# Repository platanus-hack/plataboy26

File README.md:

# Plataboy 26

A pocket game console built around an 8-pin, 10-cent RISC-V microcontroller (CH32V003:
16 KiB flash, 2 KiB RAM), a 128×64 OLED and a coin cell. It was made as merch for
Platanus Hack 26.

| | |
|---|---|
| CPU | WCH CH32V003J4M6: 32-bit RISC-V (QingKe V2A core, RV32EC, no hardware multiplier), 8-pin SOP, up to 48 MHz |
| Flash | 16 KiB, holds the game being played |
| RAM | 2 KiB |
| Storage | 128 KiB I2C EEPROM (AT24CM01): the compressed game library, game data and saves |
| Display | 0.96" monochrome OLED, 128×64, SSD1306 over I2C at 400 kHz |
| Input | four directions, A and B |
| Sound | magnetic buzzer on one pin |
| Power | CR2032 coin cell or, better, a rechargeable LIR2032 (see the note below); slide switch |
| Size | 35.56 × 54.8 mm, two layers |

> [!IMPORTANT]
> **About the battery.** The console draws far more current than a coin cell is made for:
> 17 mA in the menu and up to 33 mA in a game with a bright screen, measured on a board at 3.3 V
> (about 20 mA in a typical game). Coin cells are rated at a fraction of a milliamp.
>
> - **The CR2032 that comes with the board does not last long.** Expect a few hours of play,
>   about 6 at best, and less with bright games or sound. Under this load its voltage sags, so
>   the screen dims and the low-battery beep (below 2.8 V) comes well before the cell is empty.
>   It cannot be recharged: never put a CR2032 in a charger.
> - **A rechargeable LIR2032 is the better choice.** It holds less (35–70 mAh depending on the
>   brand, against roughly 120 mAh usable from a CR2032 at this current), so a charge gives
>   about 2 to 3 hours, but it delivers the current without sagging and can be recharged
>   hundreds of times in an external LIR2032 charger. It fits the same holder with no changes:
>   the board, like the original console, is designed for either cell.
>   A source of good cells: [this AliExpress listing](https://www.aliexpress.com/item/1005008569843235.html).
>
> To stretch either one, lower the contrast in the menu's Settings card (the lowest level takes
> the typical draw from about 20 mA to 12 mA) and switch the console off when not playing. These
> play times are estimates from the measured current and typical cell capacities, not from
> timed runs.

This repository holds everything needed to build one and to write games for it:

| | |
|---|---|
| [`hardware/`](hardware/) | board rev. 1.3.1: circuit, PCB, manufacturing package, checks, 3D model |
| [`games/`](games/) | the ported games, the starter template and the board test programs |
| [`firmware/`](firmware/) | the game library: menu, loader kernel and the packer that fills the EEPROM |
| [`sim/`](sim/) | a simulator that runs the unmodified firmware binaries (CLI and browser) |
| [`art/`](art/) | boot animation and the menu cards of the games |
| [`tools/`](tools/) | `setup.sh`, which downloads the RISC-V GCC toolchain |

## Based on wagiminator's CH32V003 Mini Game Console

The console is a derivative of the
**[CH32V003 Mini Game Console](https://github.com/wagiminator/CH32V003-GameConsole)** by
Stefan Wagner (wagiminator), published under
[CC BY-SA 3.0](https://creativecommons.org/licenses/by-sa/3.0/). The original board (rev. 1.1
here), its driver files and its "Tiny" games (ports of the
[TinyJoypad](https://www.tinyjoypad.com/) games by Daniel Champagne) are his work. The board in
this repository is shared under the same license.

### What changed from the original

**Hardware** (details and the checks behind each point in [`hardware/README.md`](hardware/README.md)):

- **External memory.** A 128 KiB I2C EEPROM (AT24CM01) with its decoupling capacitor, on the
  OLED's bus. The original holds one game at a time in the MCU's 16 KiB of flash; the EEPROM
  holds a compressed library of games, their data and their saves. No MCU pin changes.
- **I2C pull-ups** on the board (2 × 10 kΩ). The original relied on those of the OLED module.
- **A second action button, B.** All eight MCU pins were taken, so B shares the pin of A through
  a resistor divider and is read with the ADC. Games written for the original see only A and run
  unchanged.
- **Parts moved.** A and the buzzer moved to make room for B (A up-right, B down-left, buzzer in
  the bottom-right corner). Every other part keeps its original position, and every original net
  is reproduced (checked against the original Gerbers).
- **Board 4 mm taller** (35.56 × 54.8 mm), with three M2 mounting holes: top corners and bottom
  centre.
- **LCSC footprints** for every assembled part, so that the assembly house places them as drawn.
  That check found the coin cell holder reversed in the first layout.
- **New artwork**: black solder mask, white silkscreen, event logos on the front, a banana
  version of the Pioneer plaque on the back.
- **Generated, not drawn.** The circuit is a Python (SKiDL) file and the PCB is placed, routed
  and checked by scripts (`hardware/make.sh`).

**Software:**

- **Game library firmware.** A menu with a boot animation and a picture card per game. Choosing a
  game decompresses it from the EEPROM into the MCU's flash through a loader kernel of under
  1 KiB, in one to two seconds. UP + DOWN held for two seconds returns to the menu.
- **Driver additions** shared by all games (`games/common/`): the B button, joypad thresholds
  calibrated per board at power-on, a low-battery beep, a shorter buzzer pulse that draws less
  from the coin cell, and a CPU-exception handler that returns to the menu.
- **Larger games than 16 KiB allows**: code overlays and data read from the EEPROM, and fixed
  save slots per game.
- **A simulator** of the whole console, to develop without the hardware.

## Board rev. 1.3.1

| Signal | Pin | Circuit |
|---|---|---|
| OLED + EEPROM, SDA / SCL | PC1 / PC2 | SSD1306 128×64 module at I2C 0x3C; AT24CM01 at 0x50 / 0x51; 10 kΩ pull-ups |
| Joypad | PC4 (ADC ch. 2) | each direction connects VCC through 8k2 (U) / 3k9 (D) / 20k (R) / 2k (L), 2k pull-down |
| A / B | PA2 (ADC ch. 0) | A: switch to GND. B: 100 kΩ to GND against a 10 kΩ pull-up (0.91 VDD) |
| Buzzer | PA1 | MLT-5030 magnetic transducer from VCC through 22 Ω, active low |
| Supply, programming | | CR2032 (3.0 V) or LIR2032 (3.6 V); SWIO on PD1 (WCH-LinkE) |

The ready-to-order package (Gerbers, BOM and pick-and-place for JLCPCB, assembly drawings, order
sheet, STEP, KiCad board) is in [`hardware/release/`](hardware/release/). An interactive 3D
view is in `hardware/doc/3d/` (`python3 -m http.server`, then open `viewer.html`).

## Games

Each folder under `games/` builds one `.bin` for the console. The covers are the cards the menu
shows (the title screen where a game has no card).

| | Game | What it is | Original |
|---|---|---|---|
|  | **Llegamos tarde**<br>`games/llegamostarde/` | You arrived late to the hackathon and the guard locked the doors: climb the glass building, dodging what falls from the offices, with the guard climbing after you. Platanus Hack 26 edition, with the Platanus team as characters. | "Llegamos tarde a la hackathon" by [paoloose](https://github.com/paoloose/platanus-hack-25-arcade), Platanus Hack 25 arcade. No license yet; its sprites are fetched at build time |
|  | **Arduventure**<br>`games/arduventure/` | A full RPG with an overworld, battles and a save game. Its code is loaded from the EEPROM in overlays as the game moves between title, overworld, menus and battles. | [TEAM a.r.g.](https://github.com/Team-ARG-Museum/ID-46-Arduventure), Arduboy. Code MIT; story and art © TEAM a.r.g., used with permission. Fetched at build time, not kept here |
|  | **MicroCity**<br>`games/microcity/` | A city simulation: zone residential, commercial and industrial areas, connect them to power plants and roads, keep the budget and fight fires. Saves the city. | [James Howard](https://github.com/jhhoward/MicroCity), Arduboy, GPL-3.0. Fetched at build time and patched |
|  | **Just One Boss**<br>`games/justoneboss/` | Duel the magic mirror on a stage of 8 × 5 tiles: collect the magic tiles while dodging his cards, lasers, flowers, coins and reflections, through four phases. | [ayla~nonsense](https://github.com/aylanonsense/just-one-boss), PICO-8. Logic rewritten as bytecode; the cart is fetched for its sound effects |
|  | **Hopper**<br>`games/hopper/` | Jump from panel to panel and keep going up; fall off the bottom and the game is over. Keeps the ten best scores. | [OBONO](https://github.com/obono/ArduboyWorks/tree/master/hopper), Arduboy, MIT (`LICENSE.hopper`) |
|  | **Nitro Nonsense**<br>`games/nitro_nonsense/` | A four-car 3D racer seen from behind, with nitro on A and a cannon on B. First to three wins. | Written for this console by [aberguecio](https://github.com/aberguecio/nitro-nonsense-plataboy); see its `README.md` and `THIRD_PARTY.md` |
|  | **The Tiny games**<br>`games/tiny/` | The 12 games of the original console: Invaders, Arkanoid, Pacman, Tris, Boulder, Bubble, Doom, Karate, Lander, Run, Shooter and Conway's Game of Life. Rebuilt from the unmodified sources with the driver additions. | [Stefan Wagner](https://github.com/wagiminator/CH32V003-GameConsole), CC BY-SA 3.0. Invaders, Arkanoid, Pacman and Tris were first written by [Daniel Champagne](https://www.tinyjoypad.com/) for the ATtiny85, and Lander by [tscha70](https://github.com/tscha70/TinyLanderV1.0) |

Also under `games/`:

| Folder | |
|---|---|
| `template/` | "Catch", the starter game: copy it to start your own (`make new NAME=my_game`) |
| `common/` | driver additions shared by all games |
| `board_test/`, `eeprom_test/`, `cpi_bench/` | board bring-up test, EEPROM test, CPU timing calibration |

The library shipped on the boards (`firmware/library.full.json`, `make -C firmware full`) holds
Llegamos tarde, Arduventure, MicroCity, Just One Boss, Hopper, Tiny Lander, Tiny Conway and
Nitro Nonsense. Compressed, they fill the 128 KiB EEPROM to the last 125 bytes.

## Quick start

Needs a C compiler, Node 18 or later, python3 and curl (macOS or Linux). Nothing is installed
outside this folder.

```sh
make setup                           # once: RISC-V toolchain into tools/ + the simulator CLI
make play                            # the published games in the browser → http://localhost:8088/
```

`make play` alone works right after cloning: the browser core (`sim/web/chsim.wasm`) and the game
binaries are in the repository.

To write a game:

```sh
make new NAME=my_game                # copy of games/template
cd games/my_game
make sim                             # builds and serves it; run `make` in another terminal
                                     # after editing src/main.c and the browser reloads
make test                            # headless 5 s run + screenshot to bin/screen.png
make flash                           # real hardware via WCH-LinkE (pip install rvprog)
```

`make check` at the top level runs the simulator's regression check and the firmware's
end-to-end tests.

Controls in the simulator: arrows / WASD = joypad, Space / X = A, Z / C = B, P = pause,
R = power-cycle, F = fullscreen, F2 / F4 = save / load state. Gamepads and touch also work.

Building the game library and flashing it are separate steps.

**Build** (macOS or Linux; on Windows, in WSL):

```sh
make -C firmware                     # default library → firmware/build/flash.bin, eeprom.bin, writer/
make -C firmware test                # end-to-end tests in the simulator
```

**Flash** a built library. You need a **WCH-LinkE** programmer (the "E" version, in RISC-V
mode; for example [this one on AliExpress](https://www.aliexpress.com/item/1005005180653105.html)),
wired to the board's VCC, GND and DIO pads. This step needs no toolchain, only the built files
and a flashing tool you install yourself: [`rvprog`](https://pypi.org/project/rvprog/)
(`pip install rvprog`) or [`wlink`](https://github.com/ch32-rs/wlink).

```sh
make flash                           # Linux / macOS, from firmware/build (B=build-full for another)
make dist                            # → firmware/dist/plataboy26-default/ and .zip
```

`make dist` makes a folder with the built library, `flash.sh` (Linux / macOS), `flash.bat`
(Windows) and a `README.txt` with the driver setup for each system. Copy it to any computer and
run the script there: it writes the EEPROM library in chunks, then the firmware, board after
board. The folder holds only data files and the two scripts, no executables.

To choose which games go into the EEPROM, `make pick` opens a checklist in the terminal:

```
> [x] Hopper            10471
  [x] MicroCity         16462  data 7711 B at 0x179A0, save at 0x1F600
  [ ] Tiny Doom         10176
   -  Arduventure              not built: sh fetch.sh && make, in games/arduventure

[#####################.............................] 53656 / 126596 bytes
5 games + menu (6851 B).  fits: 72940 bytes free
```

Space selects a game, `[` and `]` change its place in the menu, W writes. Every change is
checked with the packer's own placement, so the total can never pass the 128 KiB: a selection
that does not fit is not written. The result is `firmware/library.custom.json`, built into
`firmware/build-custom/` (flash it with `make flash B=build-custom`). The games on offer are
listed in `firmware/catalog.json`.

The full library (`make -C firmware full`) needs each port built first: `sh fetch.sh` where
there is one, then `make`, in its folder under `games/`. The Tiny games and the hardware check
against the original Gerbers read the original project from `ref/`, which is not part of this
repository:

```sh
git clone https://github.com/wagiminator/CH32V003-GameConsole ref/CH32V003-GameConsole
```

## Simulator

No existing simulator could run these games (Wokwi, QEMU and Renode have no CH32V003 machine),
so `sim/` is a dedicated one. The same `.bin` that runs in it is the one flashed to the board.

| Layer | Choice | Why |
|---|---|---|
| CPU + SoC core | C, one translation unit, plain-struct state | fast interpreter (~130 MIPS native), portable, save state = `memcpy` |
| Browser | WebAssembly (clang `--target=wasm32`, no Emscripten, 41 KB) | same code as the CLI, so identical behaviour |
| Headless | native `chsim` CLI | automated tests, screenshots, scripted input |
| UI | dependency-free HTML/CSS/JS + Web Audio | nothing to install, hot reload |

What is simulated:

* **CPU**: RV32EC + Zicsr with QingKe PFIC vectored interrupts, hardware prologue, `mret`, WFI
  and WFE. Illegal instructions and misaligned or unmapped accesses raise exceptions.
* **Timing**: a cycle model per instruction class plus flash wait states at 48 MHz. All
  peripherals run on the same cycle counter, so delays, frame pacing, I2C and audio keep their
  real relationships.
* **Peripherals**: RCC clock tree, SysTick, GPIO, AFIO/EXTI, ADC, I2C1 master (bit-accurate
  durations), DMA1, IWDG, PWR/AWU, USART1 TX, flash programming.
* **Board**: SSD1306 (the command set that matters on 128×64; GDDRAM powers up random), the
  AT24CM01 EEPROM including write-cycle NACKs, the joypad resistor ladder computed from the
  actual network, the A/B divider, and the buzzer as time-integrated current at 48 kHz.

Not modelled (accesses are logged in the Debug tab): TIM1/TIM2, SPI, OPA, WWDG, I2C slave mode,
SSD1306 hardware scrolling.

The per-instruction cycle counts of the QingKe V2A core are not documented by WCH; the default
model is an estimate. `games/cpi_bench` measures them on a real board, and the values can be
entered under Hardware → CPU timing model. Game speed is mostly set by I2C bus time (a full
frame is 1 024 bytes, about 23 ms at 400 kHz) and SysTick waits, both modelled exactly.

Development notes:

* `make -C sim` rebuilds the CLI and the WASM core (the latter needs `brew install llvm lld`; a
  prebuilt `sim/web/chsim.wasm` is included). `make -C sim check` runs every bundled game
  headless with scripted input and compares the final frame against `sim/tools/golden.txt`.
* `sim/chsim <fw.bin|.hex> -t ms -p btn@from-to -s ms:file.pgm -a audio.raw`: scripted headless runs.
* Load `.elf` files in the UI to get symbol names for the PC and for fault reports.

## Credits and licenses

* Original console, driver files (`games/*/src`) and Tiny games: © Stefan Wagner (wagiminator),
  CC BY-SA 3.0. The Tiny games are ports of Daniel Champagne's TinyJoypad games.
* Board rev. 1.3.1 in `hardware/`: derived from the original board, CC BY-SA 3.0.
* Ported games: each belongs to its author under the license given in the table above.
* Footprints and 3D models in `hardware/footprints/` come from LCSC / EasyEDA.

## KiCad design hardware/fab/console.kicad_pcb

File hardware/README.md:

# Board rev. 1.3.1: 128 KiB EEPROM + second action button

Rev. 1.3.1 is the manufactured board. Copper, parts and placement are those of rev. 1.3 (the
silkscreen still reads `v1.3`, and the files in `fab/` keep that name); the `.1` is the
manufacturing package, in which the assembler sources and hand-solders the OLED module
(H1, EB096-01-04G-WB).

Rev. 1.1 is [wagiminator's published board](https://github.com/wagiminator/CH32V003-GameConsole)
(CC BY-SA 3.0). Rev. 1.3 keeps every rev. 1.1 net. All parts keep their rev. 1.1 position except
A (fire) and the buzzer, which move to make room for B. Added parts:

| Ref | Part | LCSC | Why |
|---|---|---|---|
| U2 | AT24CM01-SSHM-T, 1 Mbit I2C EEPROM, SOIC-8 150 mil | C68393 | 128 KiB for games and saves |
| C3 | 100 nF 0603 | C14663 | decoupling for U2 |
| R7, R8 | 10 kΩ 0603 | C25804 | SDA/SCL pull-ups (rev. 1.1 relied on the OLED module's) |
| B | 6×6 mm tact switch (same part as the others) | C23873 | second action button (rev. 1.3) |
| R9 | 100 kΩ 0603 | C25803 | B to PA2 |
| R10 | 10 kΩ 0603 | C25804 | PA2 pull-up |

**Rev. 1.2** added the EEPROM. **Rev. 1.3** adds B, with A up-right, B
down-left and the buzzer in the bottom-right corner, all on the front.

U2 sits on the existing OLED bus (PC1 = SDA, PC2 = SCL), so no MCU pin changes. A1 = A2 = WP = GND,
which puts it at I2C address **0x50** (lower 64 KiB) and **0x51** (upper 64 KiB), next to the
OLED at 0x3C, and keeps it writable.

**B shares PA2 with A** (all 8 pins are in use). A pulls PA2 to 0 V; B pulls it to 0.91 VDD
through R9 against R10. Every existing game reads PA2 as a digital input and keeps working:
to it, B is "not pressed". New games read B with the ADC (PA2 = channel A0):
`JOY_b_pressed()` in `games/template/src/driver.h`. Idle reads about 1023, B 924–954, A 0. **A and B
pressed together read as A**; B with any direction works. The first assembled boards read idle
lower than computed (972 on the sample board), so the driver samples PA2 with the long ADC
sample time and decides B relative to the idle level each board learns, not a fixed window.

**Do not order** C36057 (AT24CM01-**SHD**-T). It is the 208 mil wide body and won't fit the
footprint. Second source: ST M24M01-RMN6TP (same pinout). The 24LC1025 is **not** pin compatible.

## Files

| | |
|---|---|
| `release/plataboy26_v1.3.1_manufacturing.zip` | **the package sent to the fab**: order sheet, Gerbers, BOM/CPL, assembly drawings, renders, STEP, KiCad source |
| `fab/console_v1.3_gerbers.zip` | Gerbers + Excellon drill (2 layers, 35.56 × 54.8 mm, 1.6 mm) |
| `fab/console_v1.3_bom.csv`, `fab/console_v1.3_cpl.csv` | BOM and pick-and-place in JLCPCB format (H1 = OLED module, hand-soldered) |
| `fab/console.kicad_pcb` + `.kicad_pro` | the board, opens in KiCad 10 |
| `fab/console_v1.3_{top,bottom}.{png,pdf}` | renders / plots |
| `fab/console_v1.3.step` | 3D model of the assembled board for enclosure design (STEP, mm) |
| `doc/3d/` | `viewer.html` + `console_v1.3.glb` (interactive 3D, serve the folder: `python3 -m http.server`), `side_annotated.png`, `iso_*.png`, measured `heights.json` |
| `console.py` | **the circuit** (SKiDL, Python): single source of truth |
| `footprints/lcsc.pretty`, `lcsc.3dshapes`, `lcsc.kicad_sym` | LCSC's own footprints, 3D models and symbols for the BOM part numbers (`easyeda2kicad`), with two fixes applied by `footprints.py` |
| `footprints.py` | OLED header footprint (no LCSC part) + fixes to the LCSC footprints |
| `pcb.py` | placement, outline, silkscreen, GND pours and stitching (KiCad's Python) |
| `verify/` | Gerber net extraction and the checks below |
| `make.sh` | whole pipeline; `doc/make_compare.sh` rebuilds the picture |

`sh make.sh` regenerates everything. It needs `tools/venv` (skidl, gerbonara, numpy,
scipy, pillow), KiCad 10 (`/Applications/KiCad` or the unpacked DMG in `tools/kicad-dl/mnt`),
Java 21 and Freerouting 2.1 (`tools/freerouting`).

## Verification (all automated in make.sh)

1. **The circuit matches the shipped board.** The netlist of the rev. 1.1 board was traced
   from its Gerbers: copper areas on both layers joined through every plated hole. It matches
   `console.py` net for net on all 47 original pins (`verify/check_netlist.py`). This also
   settled what the PDF schematic leaves open: MCU pin 1 orientation, battery tab polarity,
   the live buzzer pad, and which 2 kΩ resistor is the pull-down.
2. **ERC** (SKiDL): no errors or warnings.
3. **Footprints are LCSC's own, and pin meanings agree with LCSC** (`verify/check_footprints.py`).
   Every assembled part uses the footprint LCSC publishes for its part number, which is
   what JLCPCB uses to orient parts. Every pin of U1, U2, the buzzer and the battery holder
   carries the net that LCSC's pin names call for (MCU PC1/SDA, PC2/SCL, PC4/A2 ...;
   EEPROM SDA, SCL, A1/A2/WP; buzzer +/-; the "+" printed on the holder's footprint). This
   check caught a real problem in the first layout: copied from rev. 1.1, the battery
   holder footprint had pad 1 (+) on the opposite tab to LCSC's, so the factory would
   likely have soldered the holder in reverse. It also caught two flaws in LCSC's
   converted footprints (plated peg holes on the slide switch, header silkscreen off the
   board), which `footprints.py` fixes.
4. **Placement:** every rev. 1.1 part is placed so that its pads land on the rev. 1.1 pads.
   The offset is at most 0.25 mm, except the battery tabs, where LCSC's pads sit 0.6 mm further in
   than rev. 1.1's. Both overlap the holder's tabs (LCSC: 31.3 mm lead span).
5. **DRC** (KiCad, JLCPCB/PCBWay standard rules: 0.15 mm clearance and track, 0.3 mm
   drill): 0 violations, 0 unconnected pads. The router is retried until this holds.
6. **The fab files implement the circuit.** The generated Gerbers are traced again
   and compared with the netlist: 85 pins, 22 nets, exact match (`verify/check_fab.py`).
   A deliberate SDA/SCL swap is reported as a mismatch, so the check does catch errors.
7. **Electrical budget** (AT24CM01 datasheet):
   - Supply: 1.7 to 5.5 V covers CR2032 (3.0 V) and LIR2032 (3.6 V).
   - Current: 3 µA standby at 3.6 V, 2 mA while reading; zero with the power switch off.
   - Bus: R7/R8 (10 kΩ) in parallel with the module's typical 4.7 kΩ give about 3.2 kΩ. With
     about 50 pF on the bus, the rise time is about 0.14 µs, under the 0.3 µs fast-mode limit;
     the sink current is 1.1 mA, under the 3 mA limit. Without the module, 10 kΩ alone gives
     0.42 µs, enough to program the EEPROM at 100 kHz.
   - Write cycle: 5 ms maximum, with acknowledge polling. Endurance: 1 M cycles.
7b. **Buttons, worst case** (`verify/check_buttons.py`, CH32V003 datasheet V1.1, tables 3-16
   and 3-24). The check covers 1 % resistors, internal pull-up 35–55 kΩ or off, supply 2.8–3.6 V,
   and ADC error ±4 LSB:
   - B alone gives at least 2.54 V at 2.8 V supply. VIH is 1.71 V, so old games never see B.
   - A gives 0 V, below VIL.
   - The ADC reads B at 924–954 with idle at 1019 or more, and A at most 4. B is decided against
     the idle level the board learns; the check passes for idle 1023 and for 972 (the sample board).
   - The PA2 source impedance is 9.0 kΩ, under the 10 kΩ the ADC accuracy figures assume.
   - All 8 joypad directions and diagonals stay inside their decoding windows.
   - Simulator: `games/board_test` decodes every button and combination. All 13
     published games produce the identical final frame with B held for the whole run.
8. **Firmware against the model, and the model against the vendor:** `games/eeprom_test`
   passes in the simulator (AT24CM01 model including tWR NACKs and the 0x51 bank). To
   check the simulator independently of my own code, WCH's official CH32V003 example
   `EVT/EXAM/I2C/I2C_EEPROM` (silicon-tested by the vendor; changed only to 16-bit
   addressing and a 6 ms write delay for this chip) runs unmodified and reads back
   "CH32V00x I2C TEST". `EE_read_safe()` reproduces WCH's exact read sequence as a
   fallback for the loader (CRC check, then retry), in case the fast sequential read
   behaves differently on silicon.

## Artwork (silkscreen)

**Colours:** black solder mask, white silkscreen. They are written into the board's stackup
(`pcb.py colours`), but Gerbers carry no colour, so **select "Black" solder mask and "White"
silkscreen in the fab's order form.**

- **Front (layout A3):**
  - PH↗26 under the screen.
  - "platanus hack [26]" along the left edge and "STGO 20-22.NOV.26" along the right edge.
  - PLATABOY.26 left of the DOWN button.
  - The full Platanus logo and Buk in the bottom strip, either side of the centre hole. Rev. 1.3 is 4 mm taller than rev. 1.1 (35.56 × 54.8 mm). Its three M2 holes
  (2.2 mm) sit at the top corners and the bottom centre, for a 3D-printed enclosure.
  - Sources are in `doc/art/logos/`, converted by `logos_to_silk.py`; placement is
    `FRONT_LOGOS` in `pcb.py`; `front_preview.py` tries other layouts on the routed board.
- **Back:** the banana Pioneer plaque, 30 × 23.8 mm (`doc/art/make_plaque.py` →
  `art_to_silk.py`). No back-side tracks or vias run under it.
- **Print limits:**
  - Lines thinner than about 0.15 mm do not print.
  - Buk stays clean down to about 1.5 mm tall, and the Platanus mark down to 2.0 mm
    (`doc/art/small_logo_sizes.png`).
  - The "platanus" lettering is 0.03 mm bolder than the brand font so that it prints at 1.75 mm.
- **Back:** "github.com/platanus-hack/plataboy26" under the coin cell. The CC BY-SA credit to
  wagiminator's original design lives in that repository's README.
- **3D mockup:** `sh doc/3d/build.sh` builds `doc/3d/index.html` + `console_v1.3.glb`.
  `fix_glb.py` makes the mask opaque and lifts the silkscreen so browsers draw it cleanly.
  Serve the folder with `python3 -m http.server`. `fab/console_v1.3.step` is the board for CAD.

## Heights (measured from the 3D models)

| Front, above the board | | Back, below the board | |
|---|---|---|---|
| programming header H2 | 8.5 mm | CR2032 holder | 5.6 mm |
| buttons A, B, D-pad | 6.0 mm | EEPROM U2 | 1.8 mm |
| OLED glass (module on 2.5 mm header) | 4.9 mm | everything else | < 1.8 mm |
| power switch / buzzer | 3.2 / 2.0 mm | | |

All six buttons are the same part and the same height, 1.1 mm above the screen glass. Total
thickness is 13.2 mm. The 3-pin programming header adds 2.5 mm on top. Leave it unfitted in
production (program through pogo pins or a clip) unless the enclosure leaves room for it.

## What software cannot prove

- That JLCPCB's placement preview shows every part correctly; look at it before paying.
  With LCSC footprints it should, but U1, U2, B1 and the buzzer are worth a glance.
- Analog and mechanical reality: OLED module pinout from your supplier (must be
  GND VCC SCL SDA), switch feel, battery contact, enclosure fit.

## Bring-up

Flash `games/board_test` on a new board. Expected: "EEPROM PASS", and each button lights its
own letter. "AB" reads about 1023 idle, about 940 with B, and 0 with A (see the note on the
learned idle level above). The joypad ladder is calibrated per board by the menu firmware at
power-on (`games/common/joycal.h`, checked by `verify/check_joycal.py`).

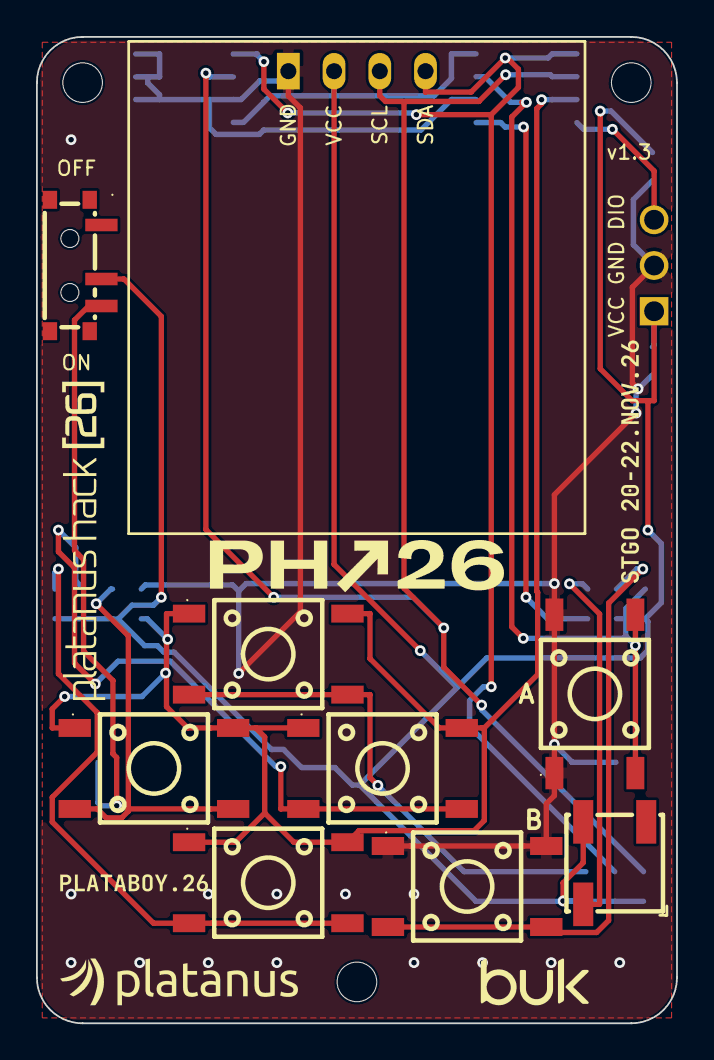
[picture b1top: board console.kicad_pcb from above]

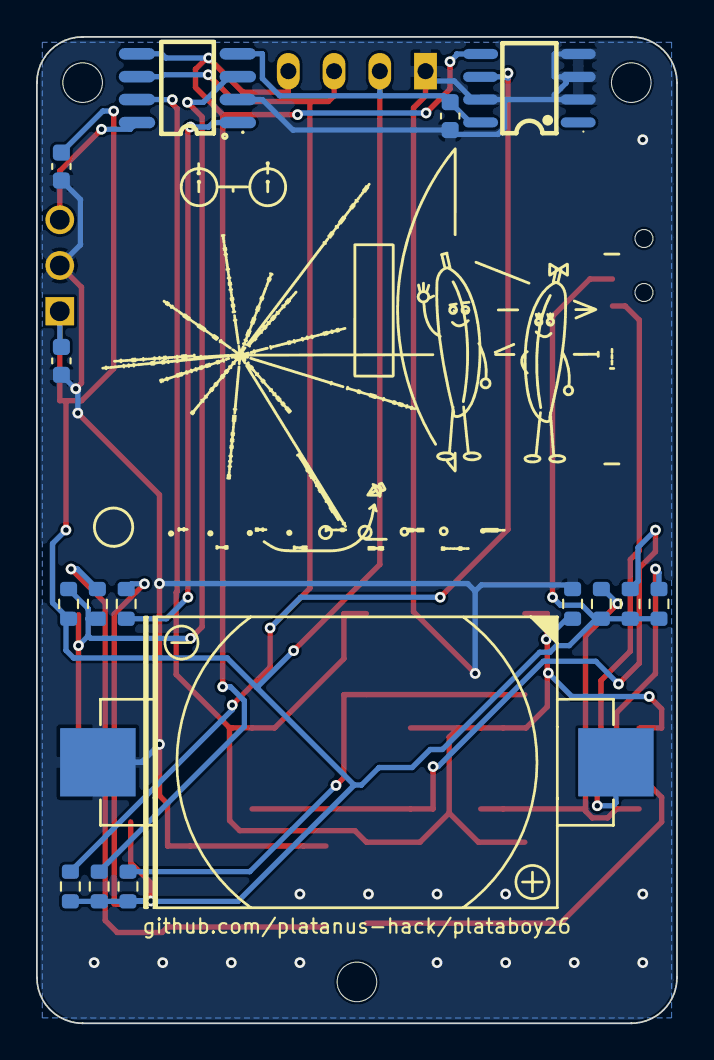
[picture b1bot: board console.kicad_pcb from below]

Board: 2 copper layers, 35.6 x 54.8 mm, 29 parts (16 on the bottom side), 15 nets.

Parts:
ACT: 6x6mm; SW-SMD_4P-L6.0-W6.0-P4.50-LS9.0_C23873
B: 6x6mm; SW-SMD_4P-L6.0-W6.0-P4.50-LS9.0_C23873
B1: CR2032; BAT-TH_CR2032-BS-6-1
BUZZER1: MLT-5030; BUZ-SMD_3P-L5.2-W5.2-P3.50-BR
C1, C3: 100n; C_0603_1608Metric
C2: 10u; C_0603_1608Metric
DOWN: 6x6mm; SW-SMD_4P-L6.0-W6.0-P4.50-LS9.0_C23873
H1: OLED; OLED_Header_1x04_P2.54mm
H2: SWIO; HDR-TH_3P-P2.54-V-M-1
LEFT: 6x6mm; SW-SMD_4P-L6.0-W6.0-P4.50-LS9.0_C23873
MH1, MH2, MH3: MountingHole; MountingHole_2.2mm_M2
R1: 22R; R_0603_1608Metric
R2: 8k2; R_0603_1608Metric
R3: 3k9; R_0603_1608Metric
R4: 20k; R_0603_1608Metric
R5, R6: 2k; R_0603_1608Metric
R7, R8, R10: 10k; R_0603_1608Metric
R9: 100k; R_0603_1608Metric
RIGHT: 6x6mm; SW-SMD_4P-L6.0-W6.0-P4.50-LS9.0_C23873
SW1: POWER; SW-SMD_SS-1290L-GLL-1.5MM
U1: CH32V003J4M6; SOP-8_L4.9-W3.8-P1.27-LS6.0-BL
U2: AT24CM01-SSHM-T; SOIC-8_L5.0-W4.0-P1.27-LS6.0-BL
UP: 6x6mm; SW-SMD_4P-L6.0-W6.0-P4.50-LS9.0_C23873

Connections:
ACT: ACT.3, ACT.4, R9.1, R10.2, U1.3
BEEP: R1.1, U1.1
BUZ: BUZZER1.3, R1.2
DIO: H2.3, U1.8
GND: ACT.1, ACT.2, B.1, B.2, B1.2, C1.1, C2.1, C3.1, H1.1, H2.2, R6.2, U1.2, U2.2, U2.3, U2.4, U2.7
PAD: DOWN.1, DOWN.2, LEFT.1, LEFT.2, R6.1, RIGHT.1, RIGHT.2, U1.7, UP.1, UP.2
SCL: H1.3, R8.2, U1.6, U2.6
SDA: H1.4, R7.2, U1.5, U2.5
SW_B: B.3, B.4, R9.2
SW_DOWN: DOWN.3, DOWN.4, R3.2
SW_LEFT: LEFT.3, LEFT.4, R5.2
SW_RIGHT: R4.2, RIGHT.3, RIGHT.4
SW_UP: R2.2, UP.3, UP.4
VBAT: B1.1, SW1.3
VCC: BUZZER1.2, C1.2, C2.2, C3.2, H1.2, H2.1, R2.1, R3.1, R4.1, R5.1, R7.1, R8.1, R10.1, SW1.2, U1.4, U2.8

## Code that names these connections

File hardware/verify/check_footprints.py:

"""Check footprints and pin meaning against LCSC's own data for the BOM part numbers.

JLCPCB orients parts using LCSC's footprints. Rev. 1.2 uses those footprints directly
(footprints/lcsc.pretty, from `easyeda2kicad --full --lcsc_id <part>`), so this checks:
  1. every assembled part uses the LCSC footprint of the LCSC number in the BOM
  2. polarised parts and ICs: the net on every pin agrees with LCSC's pin names
     (symbol pins from footprints/lcsc.kicad_sym; battery: the '+' printed on the
     LCSC footprint)
  3. the KiCad 0603 footprints match LCSC's 0603 footprints (orientation and pads)

    python verify/check_footprints.py
"""
import csv, math, os, re, sys
sys.path.insert(0, os.path.dirname(os.path.abspath(__file__)))
import netlist

HERE = os.path.dirname(os.path.abspath(__file__))
FP = os.path.join(HERE, '..', 'footprints')
KICAD_FP = os.environ.get('KICAD_FOOTPRINTS', '')

# expected net for each LCSC pin name: (LCSC part, pin name) -> net
EXPECT = {
    ('C5346354', 'VDD'): 'VCC', ('C5346354', 'VSS'): 'GND', ('C5346354', 'PC1/SDA'): 'SDA',
    ('C5346354', 'PC2/SCL'): 'SCL', ('C5346354', 'PC4/A2'): 'PAD', ('C5346354', 'PA2/OSCO/A0'): 'ACT',
    ('C5346354', 'PD6/A6/OSCI'): 'BEEP', ('C5346354', 'PD4/A7'): 'DIO',
    ('C68393', 'VCC'): 'VCC', ('C68393', 'VSS'): 'GND', ('C68393', 'SDA'): 'SDA', ('C68393', 'SCL'): 'SCL',
    ('C68393', 'A1'): 'GND', ('C68393', 'A2'): 'GND', ('C68393', 'WP'): 'GND', ('C68393', 'NC'): None,
    ('C95297', '+'): 'VCC', ('C95297', '-'): 'BUZ', ('C95297', 'NC'): None,
}
PAD = re.compile(r'\(pad\s+"?([^"\s]*)"?\s+(\w+)\s+\w+\s+\(at\s+([-\d.]+)\s+([-\d.]+)(?:\s+([-\d.]+))?\)\s*\(size\s+([\d.]+)\s+([\d.]+)\)')


def symbol_pins():
    out = {}
    text = open(os.path.join(FP, 'lcsc.kicad_sym')).read()
    for blk in re.split(r'\n  \(symbol "', text)[1:]:
        lcsc = re.search(r'"LCSC Part"\s+"([^"]+)"', blk)
        if lcsc:
            out[lcsc.group(1)] = {num: name for name, num in
                                  re.findall(r'\(pin \w+ \w+.*?\(name "([^"]*)".*?\(number "([^"]*)"', blk, re.S)}
    return out


def pads(path):
    res = []
    for num, kind, x, y, rot, w, h in PAD.findall(open(path).read()):
        w, h = float(w), float(h)
        if rot and round(float(rot)) % 180 == 90: w, h = h, w
        res.append((num, float(x), float(y), w, h))
    return res


def plus_pad(path):
    """Pad nearest to a '+' drawn on the silkscreen (a short horizontal and vertical
    line crossing at their centres)."""
    lines = re.findall(r'\(fp_line \(start ([-\d.]+) ([-\d.]+)\) \(end ([-\d.]+) ([-\d.]+)\) \(layer F.SilkS\)', open(path).read())
    segs = [tuple(map(float, l)) for l in lines]
    hs = [s for s in segs if s[1] == s[3] and 0.5 < abs(s[0] - s[2]) < 1.5]
    vs = [s for s in segs if s[0] == s[2] and 0.5 < abs(s[1] - s[3]) < 1.5]
    for h in hs:
        for v in vs:
            cx, cy = (h[0] + h[2]) / 2, (v[1] + v[3]) / 2
            if abs(v[0] - cx) < 0.05 and abs(h[1] - cy) < 0.05:
                return min(pads(path), key=lambda p: math.hypot(p[1] - cx, p[2] - cy))[0]
    return None


def main():
    comps, nets = netlist.read(os.path.join(HERE, '..', 'build', 'console.net'))
    pin_net = {p: n for n, ps in nets.items() for p in ps}
    bom = {}
    for row in csv.DictReader(open(os.path.join(HERE, '..', 'build', 'bom.csv'))):
        for ref in row['Designator'].split(','): bom[ref] = row['LCSC Part #']
    syms = symbol_pins()
    errors = 0

    def fail(msg):
        nonlocal errors; errors += 1; print('FAIL', msg)

    for ref, c in sorted(comps.items()):
        lib, name = c['footprint'].split(':')
        lcsc = bom.get(ref, '')
        if lib == 'lcsc':
            text = open(os.path.join(FP, 'lcsc.pretty', name + '.kicad_mod')).read()
            m = re.search(r'"LCSC Part" "([^"]+)"', text)
            if not m or m.group(1) != lcsc and not (name.startswith('SOIC-8') or name.startswith('SOP-8')):
                # generic package footprints carry the number they were first fetched for
                fail(f'{ref}: footprint {name} belongs to {m.group(1) if m else "?"}, BOM says {lcsc}')
        for pin_num, pin_name in syms.get(lcsc, {}).items():
            key = (lcsc, pin_name)
            if key in EXPECT:
                got = pin_net.get(f'{ref}.{pin_num}')
                if got != EXPECT[key]: fail(f'{ref} pin {pin_num} ({pin_name}): net {got}, expected {EXPECT[key]}')
                else: print(f'ok   {ref:8} pin {pin_num} {pin_name:12} -> {got}')
        if lcsc == 'C70377':
            plus = plus_pad(os.path.join(FP, 'lcsc.pretty', name + '.kicad_mod'))
            got = pin_net.get(f'{ref}.{plus}')
            if got != 'VBAT': fail(f'{ref}: the + tab (pad {plus}) is on net {got}, expected VBAT')
            else: print(f'ok   {ref:8} pad {plus} next to the LCSC "+" mark -> {got}')

    for kind, mine, theirs in (('R', 'Resistor_SMD.pretty/R_0603_1608Metric', 'R0603'),
                               ('C', 'Capacitor_SMD.pretty/C_0603_1608Metric', 'C0603')):
        a = {p[0]: p for p in pads(os.path.join(KICAD_FP, mine + '.kicad_mod'))}
        b = {p[0]: p for p in pads(os.path.join(FP, '..', 'verify', 'lcsc', theirs + '.kicad_mod'))}
        err = max(math.hypot(a[n][1] - b[n][1], a[n][2] - b[n][2]) for n in a)
        (print if err < 0.15 else fail)(f'{"ok  " if err < 0.15 else ""} {kind} 0603: KiCad vs LCSC pad positions differ by {err:.2f} mm, same orientation and pin 1 side')

    print('RESULT:', 'footprints and pin meanings agree with LCSC' if not errors else f'{errors} problems')
    sys.exit(1 if errors else 0)


if __name__ == '__main__':
    main()
